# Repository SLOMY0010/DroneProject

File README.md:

# DroneProject

Custom Arduino-based quadcopter controller system with a handheld Bluetooth controller, onboard stabilization algorithms, and KiCad PCB designs for both the drone electronics and the controller.

This project was developed as part of a summer program. The goal was to design and implement the main electronics and software required for a quadcopter prototype, including wireless control, sensor-based stabilization, motor mixing, safety behavior, and PCB design.

> **Project status:** Prototype / ground-tested.  
> The system was validated on the ground, but a complete stable flight test was not achieved within the project deadline. The final prototype was limited mainly by added weight, limited motor/frame lifting capacity, and the fact that the designed PCBs were not soldered and integrated before the final presentation.

## Demo

A demonstration video is available here:

[Drone Project: Custom Quadcopter Controller System](https://youtu.be/c0thseL-vnU)

## Overview

The system is divided into two main units:

1. **Drone unit**
   - Uses the frame and motors of an MJX Bugs 3 Pro drone.
   - Replaces the original electronics with a custom Arduino-based flight controller.
   - Reads IMU and compass data.
   - Applies Kalman filtering and PID control to stabilize roll, pitch, and yaw.
   - Drives four ESC-controlled brushless motors.
   - Includes safety behavior for lost communication and landing.

2. **Handheld controller unit**
   - Built around an Arduino Nano.
   - Reads joysticks, buttons, potentiometers, switches, and an MPU-6050 sensor.
   - Sends controller input packets to the drone over Bluetooth.
   - Supports normal joystick control and experimental gyro-based control modes.

```text
Handheld Controller                         Drone Unit
-------------------                         ----------
Joysticks / buttons / pots / IMU  --->  Bluetooth  --->  Arduino Nano
                                                        |
                                                        +--> IMU + compass
                                                        +--> Kalman filter
                                                        +--> PID controller
                                                        +--> Motor mixing
                                                        +--> ESCs / motors
```

## Main Features

- Arduino Nano based controller and drone firmware.
- Bluetooth communication between controller and drone.
- 18-byte controller data packet with checksum validation.
- Kalman-filtered roll and pitch angle estimation.
- PID stabilization for roll, pitch, and yaw.
- Magnetometer-based heading hold / north-facing behavior.
- Joystick control mode.
- Experimental gyro-control mode using the handheld controller orientation.
- Experimental potentiometer-based control mode.
- Motor mixing for a quadcopter X-style layout.
- Lost-signal safety behavior that slowly reduces throttle.
- Battery voltage indication using LEDs.
- KiCad PCB designs for the drone board and controller board.

## Repository Structure

```text
.
├── controller/
│   └── controller.ino
│       Firmware for the handheld controller.
│
├── drone_hardware_serial/
│   └── drone_hardware_serial.ino
│       Main drone firmware. This is the recommended drone-side version.
│       It uses the Arduino Nano hardware serial pins for Bluetooth communication,
│       which produced smoother motor behavior during testing.
│
├── drone/
│   └── drone.ino
│       Alternative drone firmware using SoftwareSerial for Bluetooth.
│       Useful for debugging because hardware Serial remains available for the
│       Arduino Serial Monitor. However, SoftwareSerial caused unstable motor
│       behavior during powered motor testing.
│
├── testing/
│   └── testing.ino
│       Experimental/testing code used during development.
│
├── PCB-Controller-main/
│       KiCad project files for the handheld controller PCB.
│
├── drone_pcb/
│       KiCad project files for the drone-side PCB.
│
└── Libraries/
        Shared KiCad symbols/footprints used by the PCB projects.
```

## Firmware Folders

### `controller/`

This folder contains the firmware uploaded to the Arduino Nano inside the handheld controller.

The controller reads:

- Two joysticks
- Four push buttons
- Two potentiometers
- Two switches
- MPU-6050 motion sensor

It packages the input data into a `Controller` struct and sends it to the drone through a Bluetooth module. The controller also performs joystick calibration and supports a gyro-control mode where the controller's tilt is used as a roll/pitch input.

### `drone_hardware_serial/`

This is the main drone firmware and the recommended version for actual motor testing.

It uses the Arduino Nano hardware serial interface for Bluetooth communication. This was more stable than the SoftwareSerial version when the motors were powered, because SoftwareSerial timing interfered with the control loop and produced unstable PWM behavior.

The firmware handles:

- Receiving controller packets over Bluetooth
- Validating received data using a checksum
- Reading IMU data
- Reading compass/magnetometer heading
- Kalman filtering for angle estimation
- PID control for stabilization
- Quadcopter motor mixing
- ESC PWM signal generation
- Battery LED indication
- Lost-communication landing behavior

### `drone/`

This is an older/alternative drone firmware version using SoftwareSerial for Bluetooth communication.

It is still useful for debugging because the hardware serial port remains available for the Serial Monitor. However, it is not the preferred version for powered motor testing because it caused unstable PWM behavior and stronger vibration during testing.

### `testing/`

This folder contains experimental code used while testing individual parts of the project.

## Communication Protocol

The controller sends a binary packet to the drone. The packet contains button states, joystick values, potentiometer values, gyro-mode roll/pitch values, and a checksum.

Simplified structure:

```cpp
struct Controller {
    uint8_t bools; // Buttons & switches
    int16_t roll, pitch; // MPU-6050 Readings
    int16_t JLx, JLy, JRx, JRy; // Joysticks input
    int16_t PL, PR; // Potentiometers
    uint8_t checksum; 
}; // 18-Bytes
```

The checksum is calculated using XOR over the packet bytes. On the drone side, packets are rejected if the checksum is invalid or if important values are outside expected limits.

The controller sends data when input changes and also sends periodic updates so the drone can detect that the connection is still alive.

## Control and Stabilization

The flight-control logic combines sensor reading, filtering, PID control, and motor mixing.

### Angle estimation

The drone uses accelerometer and gyroscope readings to estimate roll and pitch angles. A Kalman filter is used to combine the fast response of the gyroscope with the long-term correction of the accelerometer.

### PID control

PID controllers are used to reduce the difference between the target angle and the measured angle. The target angles come from either joystick input or gyro-mode controller input.

The PID outputs are then mixed into the motor signals to adjust the four motor speeds.

### Yaw / heading behavior

The drone firmware also reads magnetometer data to estimate heading. This allows heading hold behavior when there is no yaw input, and a mode for turning the drone toward north.

### Motor mixing

The drone uses four motors in a quadcopter layout:

```text
M1 = front-left
M2 = front-right
M3 = back-right
M4 = back-left
```

The firmware combines throttle, pitch, roll, and yaw values to generate the PWM signal for each motor.

## Hardware

### Drone unit

- MJX Bugs 3 Pro frame and motors
- Arduino Nano
- HW-290 sensor module
  - MPU-6050 accelerometer/gyroscope
  - Magnetometer
  - Barometer module available on the board, but not central to the current control code
- Bluetooth module
- Four ESCs
- Custom drone PCB design in KiCad
- Temporary breadboard circuit used during final testing

### Controller unit

- Arduino Nano
- Two joysticks
- Four push buttons
- Two potentiometers
- Two switches
- MPU-6050 sensor
- Bluetooth module
- Custom controller PCB design in KiCad
- Perfboard/breadboard prototype used during testing

## PCB Designs

The project includes KiCad PCB designs for both the drone and the controller.

- `PCB-Controller-main/` contains the controller PCB project.
- `drone_pcb/` contains the drone PCB project.
- `Libraries/` contains shared KiCad symbols and footprints required by the PCB projects.

The PCBs were designed and ordered, but they were not soldered, assembled, and fully tested before the project deadline. During the final testing stage, the electronics were still tested using a small breadboard mounted on the drone.

## Software Requirements

The code is written for the Arduino environment.

Expected tools/libraries:

- Arduino IDE or Arduino CLI
- Arduino Nano board support
- Standard Arduino libraries:
  - `Wire`
  - `Servo`
  - `SoftwareSerial`
- QMC5883L compass library or a compatible `QMC5883LCompass` library

Depending on the Arduino Nano board version, you may need to select either the normal ATmega328P bootloader or the old bootloader in the Arduino IDE.

## Upload Instructions

### 1. Upload the controller firmware

Open:

```text
controller/controller.ino
```

Upload it to the Arduino Nano used in the handheld controller.

### 2. Upload the recommended drone firmware

Open:

```text
drone_hardware_serial/drone_hardware_serial.ino
```

Upload it to the Arduino Nano used on the drone.

Because this version uses hardware serial for Bluetooth, disconnect the Bluetooth module from the Arduino Nano RX/TX pins while uploading if it interferes with programming.

### 3. Optional debugging firmware

For debugging, open:

```text
drone/drone.ino
```

This version uses SoftwareSerial for Bluetooth, leaving the hardware serial port available for the Arduino Serial Monitor. It is useful for troubleshooting, but it is not recommended for powered motor testing because SoftwareSerial caused unstable motor behavior during development.

## Safety Notes

This is an experimental drone-control project, not a ready-to-fly commercial flight controller.

Before testing:

- Remove propellers during firmware upload and initial motor tests.
- Secure the drone frame before powered tests.
- Verify motor order and direction.
- Verify ESC calibration and throttle range.
- Keep the drone level and still during sensor calibration.
- Test the lost-signal behavior before attempting flight.
- Do not attempt flight until the PID gains, wiring, power system, and mechanical setup are verified.

## Results

The project successfully implemented the main parts of a custom quadcopter control system:

- Wireless controller communication
- Controller input packaging
- Checksum-based packet validation
- IMU reading and calibration
- Kalman-filtered angle estimation
- PID-based stabilization logic
- Motor mixing and ESC signal generation
- PCB designs for both the controller and drone electronics

During ground testing, the electronics and algorithms responded correctly. However, stable flight was not achieved before the deadline. The main limitations were the added prototype weight, the limited lifting capacity of the reused frame/motors, and the fact that the final PCBs were not assembled and integrated in time.

## Known Limitations

- Full stable flight was not achieved.
- The drone was tested mainly on the ground.
- The PCBs were designed but not fully soldered and validated.
- The final test setup used a breadboard, which added weight and reduced reliability.
- The reused MJX Bugs 3 Pro frame and motors had limited lifting capacity with the added custom electronics.
- Bluetooth is not ideal for a final drone communication system.
- PID values require further tuning on a lighter and more reliable hardware setup.
- The SoftwareSerial drone firmware should be treated as a debugging variant, not the recommended flight-control version.

## Future Improvements

Possible next steps:

- Assemble and test the designed PCBs.
- Move to a lighter airframe or higher-thrust motors.
- Replace Bluetooth with a more suitable radio-control communication system.
- Improve power distribution and reduce electrical noise.
- Tune the PID controller during controlled flight tests.
- Add proper mechanical mounting for the IMU to reduce vibration.
- Add camera support.
- Improve failsafe behavior and pre-flight checks.
- Add more documentation for wiring and calibration.

## Author

Abdulaziz Salem Ali Salem

Project supervisor: Dr. Sütő József

## License

No license has been specified yet. If you plan to reuse this code or hardware design, please contact the author.

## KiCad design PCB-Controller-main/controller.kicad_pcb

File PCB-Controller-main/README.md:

# PCB-Controller
KICAD PCB Controller

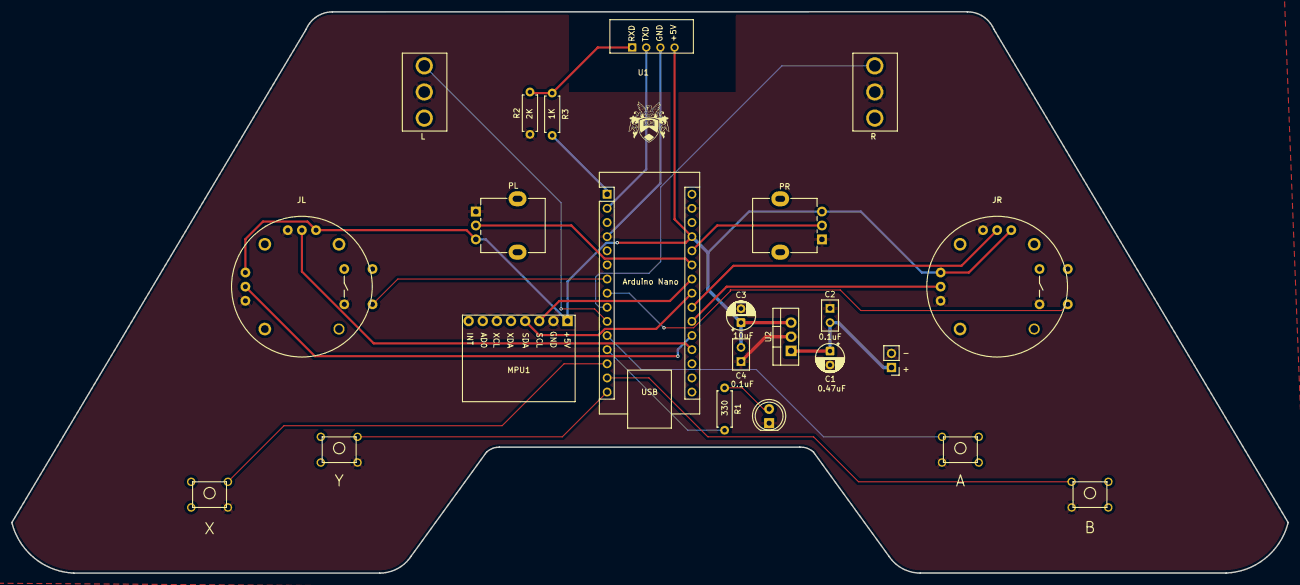
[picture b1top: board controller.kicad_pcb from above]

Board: 2 copper layers, 229.5 x 100.9 mm, 23 parts (0 on the bottom side), 24 nets.

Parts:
A: SW_Push_Dual; BTN
Arduino Nano: Arduino_Nano_v3.x; Arduino_Nano
B: SW_Push_Dual; BTN
C1: 0.47uF; CP_Radial_D5.0mm_P2.50mm
C2, C4: 0.1uF; C
C3: 10uF; CP_Radial_D5.0mm_P2.50mm
D1: LED; LED_D5.0mm
J1: Conn_01x02_Pin; PinHeader_1x02_P2.54mm_Vertical
Joystick1, Joystick2: JOYSTICK
L: SW_SPDT; TOGGLE_SWITCH
MPU1: MPU6050
PL: R_Potentiometer; Potentiometer_Alpha_RD901F-40-00D_Single_Vertical
PR: R_Potentiometer; Potentiometer_Alpha_RD901F-40-00D_Single_Vertical
R: SW_SPDT; TOGGLE_SWITCH
R1: 330; R_Axial_DIN0207_L6.3mm_D2.5mm_P7.62mm_Horizontal
R2: 2K; R_Axial_DIN0207_L6.3mm_D2.5mm_P7.62mm_Horizontal
R3: 1K; R_Axial_DIN0207_L6.3mm_D2.5mm_P7.62mm_Horizontal
U1: HC-05
U2: L7805; TO-220-3_Vertical
X: SW_Push_Dual; BTN
Y: SW_Push_Dual; BTN

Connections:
+5V: Arduino Nano.27 (+5V), C3.1, C4.1, Joystick1.1 (VCC), Joystick1.4 (VCC), Joystick2.1 (VCC), Joystick2.4 (VCC), MPU1.1 (VCC), PL.3, PR.3, U1.4 (5V), U2.3 (OUT)
GND: A.3, Arduino Nano.4 (GND), Arduino Nano.29 (GND), B.3, C1.2, C2.2, C3.2, C4.2, D1.1 (K), J1.2, Joystick1.3 (GND), Joystick1.6 (GND), Joystick1.8 (GND), Joystick2.3 (GND), Joystick2.6 (GND), Joystick2.8 (GND), L.2 (B), MPU1.2 (GND), PL.1, PR.1, R.2 (B), R2.1, U1.3 (GND), U2.2 (GND), X.4, Y.4
unnamed: Arduino Nano.19 (A0), Joystick1.5 (VOUT)
unnamed: Arduino Nano.20 (A1), Joystick1.2 (VOUT)
unnamed: Arduino Nano.21 (A2), Joystick2.2 (VOUT)
unnamed: Arduino Nano.22 (A3), Joystick2.5 (VOUT)
unnamed: Arduino Nano.23 (A4), MPU1.4 (SDA)
unnamed: Arduino Nano.24 (A5), MPU1.3 (SCL)
unnamed: Arduino Nano.25 (A6), PL.2
unnamed: Arduino Nano.26 (A7), PR.2
unnamed: Arduino Nano.2 (D0/RX), U1.2 (TXD)
unnamed: Arduino Nano.1 (D1/TX), R3.2
unnamed: Arduino Nano.7 (D4), Joystick1.9 (DOUT)
unnamed: Arduino Nano.8 (D5), Joystick2.9 (DOUT)
unnamed: Arduino Nano.9 (D6), R.3 (C)
unnamed: Arduino Nano.10 (D7), L.3 (C)
unnamed: A.1, Arduino Nano.11 (D8)
unnamed: Arduino Nano.12 (D9), R1.2
unnamed: Arduino Nano.13 (D10), X.2
unnamed: Arduino Nano.14 (D11), B.1
unnamed: Arduino Nano.15 (D12), Y.2
unnamed: D1.2 (A), R1.1
unnamed: R2.2, R3.1, U1.1 (RXD)
VCC: C1.1, C2.1, J1.1, U2.1 (IN)

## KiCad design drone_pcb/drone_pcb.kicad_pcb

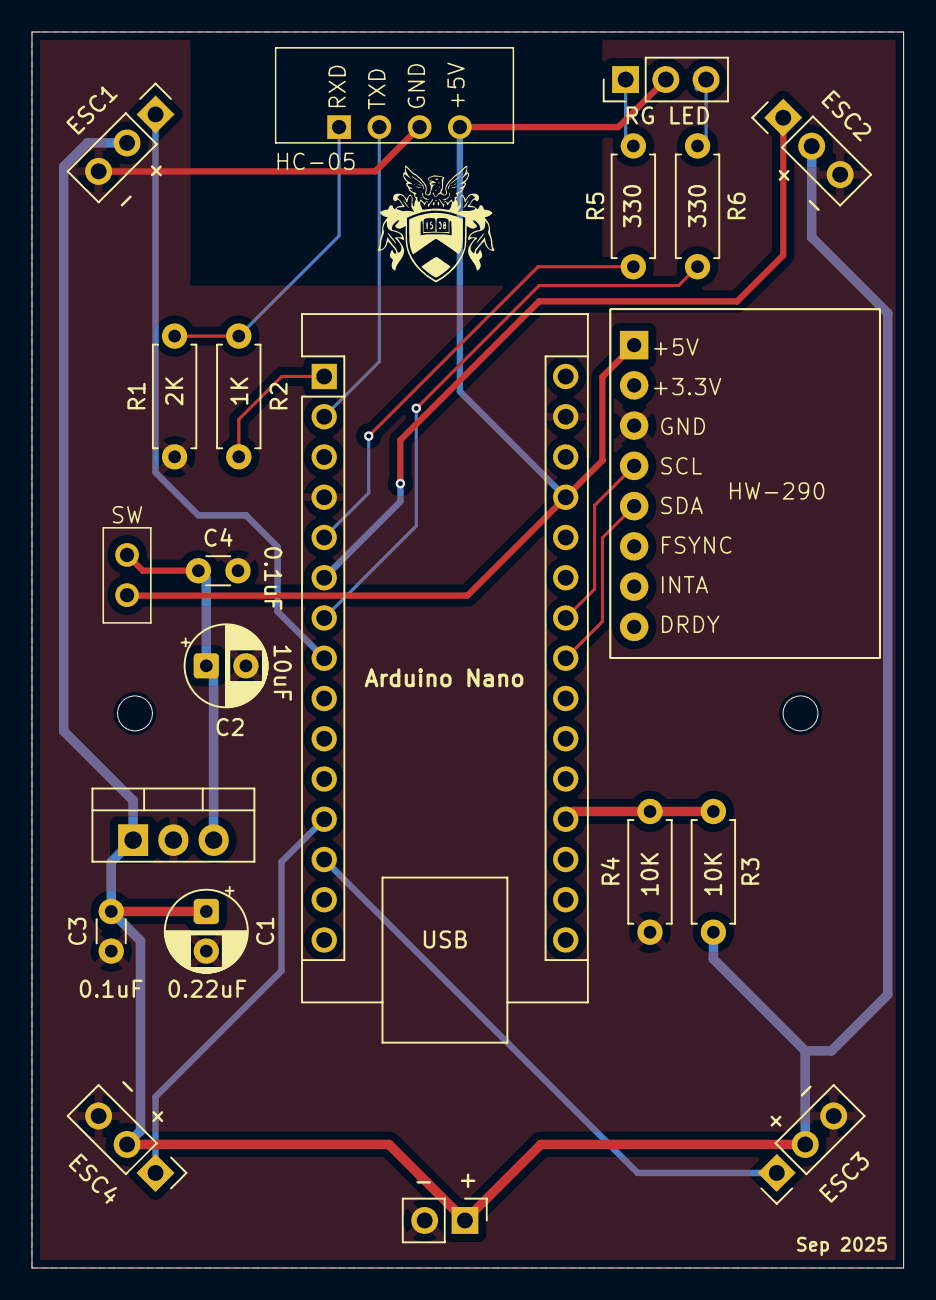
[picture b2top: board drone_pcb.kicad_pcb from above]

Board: 2 copper layers, 55.0 x 78.0 mm, 21 parts (0 on the bottom side), 18 nets.

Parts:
Arduino Nano: Arduino_Nano_v3.x; Arduino_Nano
C1: 0.22uF; CP_Radial_D5.0mm_P2.50mm
C2: 10uF; CP_Radial_D5.0mm_P2.50mm
C3, C4: 0.1uF; C_Disc_D3.0mm_W1.6mm_P2.50mm
ESC1, ESC2, ESC3, ESC4: 3-pin Header; PinHeader_1x03_P2.54mm_Vertical
HC-05: HC-05
HW-290: HW-290
J1: Conn_01x02_Pin; PinHeader_1x02_P2.54mm_Vertical
R1: 2K; R_Axial_DIN0207_L6.3mm_D2.5mm_P7.62mm_Horizontal
R2: 1K; R_Axial_DIN0207_L6.3mm_D2.5mm_P7.62mm_Horizontal
R3, R4: 10K; R_Axial_DIN0207_L6.3mm_D2.5mm_P7.62mm_Horizontal
R5, R6: 330; R_Axial_DIN0207_L6.3mm_D2.5mm_P7.62mm_Horizontal
RG LED: RG LED; PinHeader_1x03_P2.54mm_Vertical
SW: SW_SPST; SW_reg5v
U7: L7805; TO-220-3_Vertical

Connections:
+5V: Arduino Nano.27 (+5V), HC-05.4 (5V), HW-290.1 (5V), RG LED.2 (VCC), SW.2 (B)
GND: Arduino Nano.4 (GND), Arduino Nano.29 (GND), C1.2, C2.2, C3.2, C4.2, ESC1.3 (GND), ESC2.3 (GND), ESC3.3 (GND), ESC4.3 (GND), HC-05.3 (GND), HW-290.3 (GND), J1.2, R1.1, R4.2, U7.2 (GND)
unnamed: Arduino Nano.19 (A0), R3.1, R4.1
unnamed: Arduino Nano.23 (A4), HW-290.5 (SDA)
unnamed: Arduino Nano.24 (A5), HW-290.4 (SCL)
unnamed: Arduino Nano.2 (D0/RX), HC-05.2 (TXD)
unnamed: Arduino Nano.1 (D1/TX), R2.1
unnamed: Arduino Nano.5 (D2), R5.1
unnamed: Arduino Nano.6 (D3), ESC2.1 (SIG)
unnamed: Arduino Nano.7 (D4), R6.1
unnamed: Arduino Nano.8 (D5), ESC1.1 (SIG)
unnamed: Arduino Nano.12 (D9), ESC4.1 (SIG)
unnamed: Arduino Nano.13 (D10), ESC3.1 (SIG)
unnamed: C2.1, C4.1, SW.1 (A), U7.3 (OUT)
unnamed: HC-05.1 (RXD), R1.2, R2.2
unnamed: R6.2, RG LED.3 (G)
unnamed: R5.2, RG LED.1 (R)
VCC: C1.1, C3.1, ESC1.2 (VCC), ESC2.2 (VCC), ESC3.2 (VCC), ESC4.2 (VCC), J1.1, R3.2, U7.1 (IN)

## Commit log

2025-07-08 added the drone file
2025-07-09 enabled bluetooth communication
2025-07-09 implemented speed calculation for each motor, and motion control
2025-07-13 reduced stuttering by limiting communication to send only when necessary
2025-07-13 Just fixed some comments
2025-07-25 changed to hardware serial communication
2025-07-25 just made reading buttons update the new_input variable
2025-07-26 implemented accelerometer angle calculation, just from aeronautics
2025-07-31 finally implemented the kalman filter for measuring roll and pitch angles
2025-08-02 Finally figured out PID tunning
2025-08-02 updated the regular software serial drone code to the latest version
2025-08-02 Put everything into the main drone code. Not tested yet tho
2025-08-04 fixed joystick calibration
2025-08-04 added gyro flying mode to fly the drone by moving the controller
2025-08-04 stopped before testing drone with the new PID and gyroscope code
2025-08-06 started testing. NOT finished yet
2025-08-07 Tested bluetooth and gyro mode, next is testing with fans and pid tunning
2025-08-27 battery status
2025-08-27 button B lands the drone
2025-08-27 B lands
2025-08-28 did smth but bluetooth is trippin
2025-08-29 reduced packet size
2025-08-29 fixed bugs
2025-08-29 small adjustments
2025-08-30 basic PID tunning is done
2025-08-30 pressing X makes the drone face north. Not tested.
2025-08-30 gyro mode stopped working, I have no idea why. I'll fix it tomorrow
2025-08-31 Finally fixed gyro, and updated software serial version
2025-08-31 X mode is done for throttlegit status!
2025-09-10 just simple fixes
2025-09-18 Added PCB designs to the repository
2026-06-30 Created README.md
